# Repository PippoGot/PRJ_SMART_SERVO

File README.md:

# Smart Servo Project
----------------------------------------------------------------

The scope of this repository is to design a new controller board for the MG996R
hobby servo, in order to improve position accuracy and performance.

In particular, the goal is to:

- Implement a more accurate position controller;

- Implement a current controller to limit stall overheating;

- Implement a I2C interface to control the servo, for:
    + current and position readings;
    + flexible and overwritable PID controller & threshold values;
    + calibration routine to estimate motor parameter;
    + possibility of daisy-chaining more servos using a limited number of ports;

More useful things to have are:

- Thermal safety shutdown;

----------------------------------------------------------------
## Folder Structure:

- "DATASHEETS": contains all of the datasheets for the components used,
both in the original controller board and in the new developed board;

- "default servo control board": contains the KiCAD files of the reverse engineered
original servo controller board;

- "MODELS & SIMULATIONS": contains the Simulink and LTSpice models, as well as the
Matlab scripts for parameters and controller tuning;

- "SOURCE": contains all the code for the microcontroller;

- "STM32 PDFs & DATASHEET": contains the documentation of the microcontroller
applied to the board, as well as some useful PDFs for making and programming
embedded projects using the microcontroller itself;

- "STM32F103C8T6 minimum board": contains the KiCAD files of a minimum board
for any embedded project using that specific microcontroller;

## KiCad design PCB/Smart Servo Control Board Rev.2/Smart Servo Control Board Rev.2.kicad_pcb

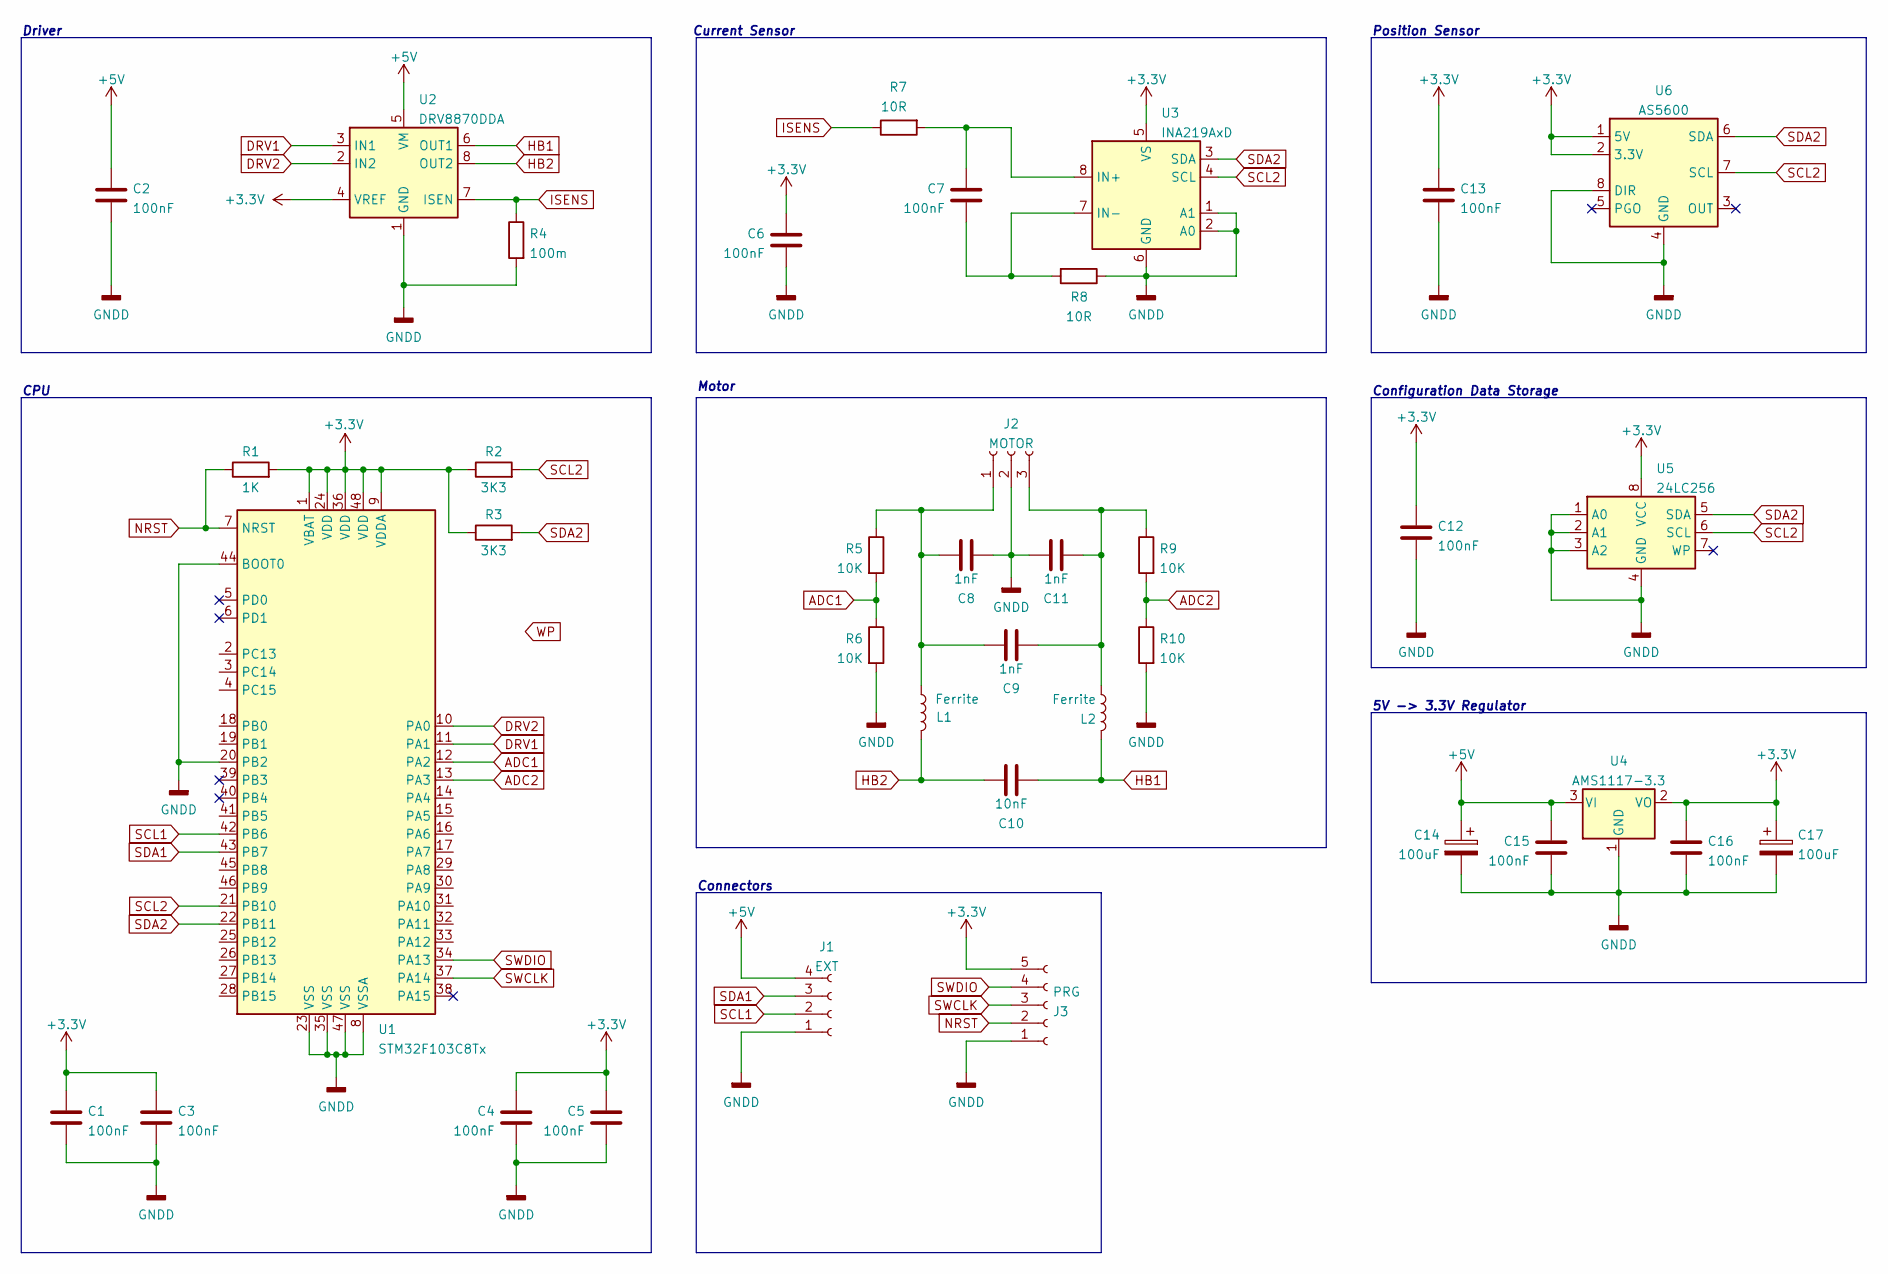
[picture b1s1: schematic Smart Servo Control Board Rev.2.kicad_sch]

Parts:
C1, C2, C3, C4, C5, C6, C7, C12, C13, C15, C16: 100nF; R_0603_1608Metric_Pad0.98x0.95mm_HandSolder
C8, C9, C11: 1nF; R_0603_1608Metric_Pad0.98x0.95mm_HandSolder
C10: 10nF; R_0603_1608Metric_Pad0.98x0.95mm_HandSolder
C14, C17: 100uF; CP_EIA-3216-10_Kemet-I
J1: EXT; Pad_1x04_P2.54mm_Vertical
J2: MOTOR; DC motor 17mm
J3: PRG; PinHeader_1x05_P2.54mm_Vertical_SMD_Pin1Left
L1, L2: Ferrite; R_0603_1608Metric_Pad0.98x0.95mm_HandSolder
R1: 1K; R_0603_1608Metric_Pad0.98x0.95mm_HandSolder
R2, R3: 3K3; R_0603_1608Metric_Pad0.98x0.95mm_HandSolder
R4: 100m; R_1206_3216Metric_Pad1.30x1.75mm_HandSolder
R5, R6, R9, R10: 10K; R_0603_1608Metric_Pad0.98x0.95mm_HandSolder
R7, R8: 10R; R_0603_1608Metric_Pad0.98x0.95mm_HandSolder
U1: STM32F103C8Tx; LQFP-48_7x7mm_P0.5mm
U2: DRV8870DDA; SOIC-8-1EP_3.9x4.9mm_P1.27mm_EP2.514x3.2mm
U3: INA219AxD; SOT-23-8
U4: AMS1117-3.3; SOT-223-3_TabPin2
U5: 24LC256; SO-8_3.9x4.9mm_P1.27mm
U6: AS5600; SO-8_3.9x4.9mm_P1.27mm

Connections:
+3V3: C1.2, C3.2, C4.2, C5.2, C6.2, C12.2, C13.2, C16.1, C17.1, J3.5, R1.2, R2.1, R3.1, U1.1 (VBAT), U1.9 (VDDA), U1.24 (VDD), U1.36 (VDD), U1.48 (VDD), U2.4 (VREF), U3.5 (VS), U4.2 (VO), U5.8 (VCC), U6.1 (5V), U6.2 (3.3V)
+5V: C2.2, C14.1, C15.1, J1.4, U2.5 (VM), U4.3 (VI)
ADC1: R5.2, R6.1, U1.12 (PA2)
ADC2: R9.2, R10.1, U1.13 (PA3)
DRV1: U1.11 (PA1), U2.3 (IN1)
DRV2: U1.10 (PA0), U2.2 (IN2)
GNDD: C1.1, C2.1, C3.1, C4.1, C5.1, C6.1, C8.2, C11.1, C12.1, C13.1, C14.2, C15.2, C16.2, C17.2, J1.1, J2.2, J3.1, R4.2, R6.2, R8.1, R10.2, U1.8 (VSSA), U1.20 (PB2), U1.23 (VSS), U1.35 (VSS), U1.44 (BOOT0), U1.47 (VSS), U2.1 (GND), U2.9 (GND), U3.1 (A1), U3.2 (A0), U3.6 (GND), U4.1 (GND), U5.1 (A0), U5.2 (A1), U5.3 (A2), U5.4 (GND), U6.4 (GND), U6.8 (DIR)
HB1: C10.2, L2.2, U2.6 (OUT1)
HB2: C10.1, L1.2, U2.8 (OUT2)
ISENS: R4.1, R7.1, U2.7 (ISEN)
NRST: J3.2, R1.1, U1.7 (NRST)
unnamed: C7.1, R7.2, U3.8 (IN+)
unnamed: C7.2, R8.2, U3.7 (IN-)
unnamed: C8.1, C9.1, J2.1, L1.1, R5.1
unnamed: C9.2, C11.2, J2.3, L2.1, R9.1
SCL1: J1.2, U1.42 (PB6)
SCL2: R2.2, U1.21 (PB10), U3.4 (SCL), U5.6 (SCL), U6.7 (SCL)
SDA1: J1.3, U1.43 (PB7)
SDA2: R3.2, U1.22 (PB11), U3.3 (SDA), U5.5 (SDA), U6.6 (SDA)
SWCLK: J3.3, U1.37 (PA14)
SWDIO: J3.4, U1.34 (PA13)

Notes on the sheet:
Current Sensor
Position Sensor
Motor
5V -> 3.3V Regulator
Driver
CPU
Connectors
Configuration Data Storage

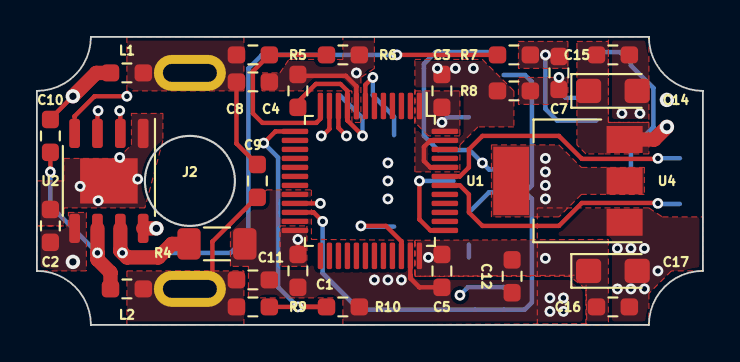
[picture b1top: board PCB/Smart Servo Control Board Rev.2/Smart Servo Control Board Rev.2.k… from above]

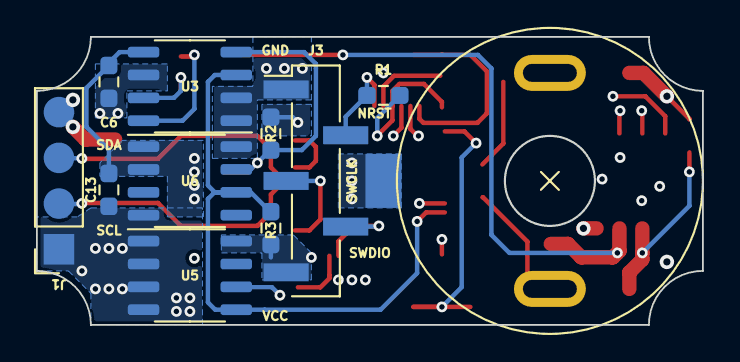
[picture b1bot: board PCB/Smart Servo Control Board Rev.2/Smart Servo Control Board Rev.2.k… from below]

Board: 4 copper layers, 37.0 x 16.0 mm, 38 parts (10 on the bottom side), 21 nets.

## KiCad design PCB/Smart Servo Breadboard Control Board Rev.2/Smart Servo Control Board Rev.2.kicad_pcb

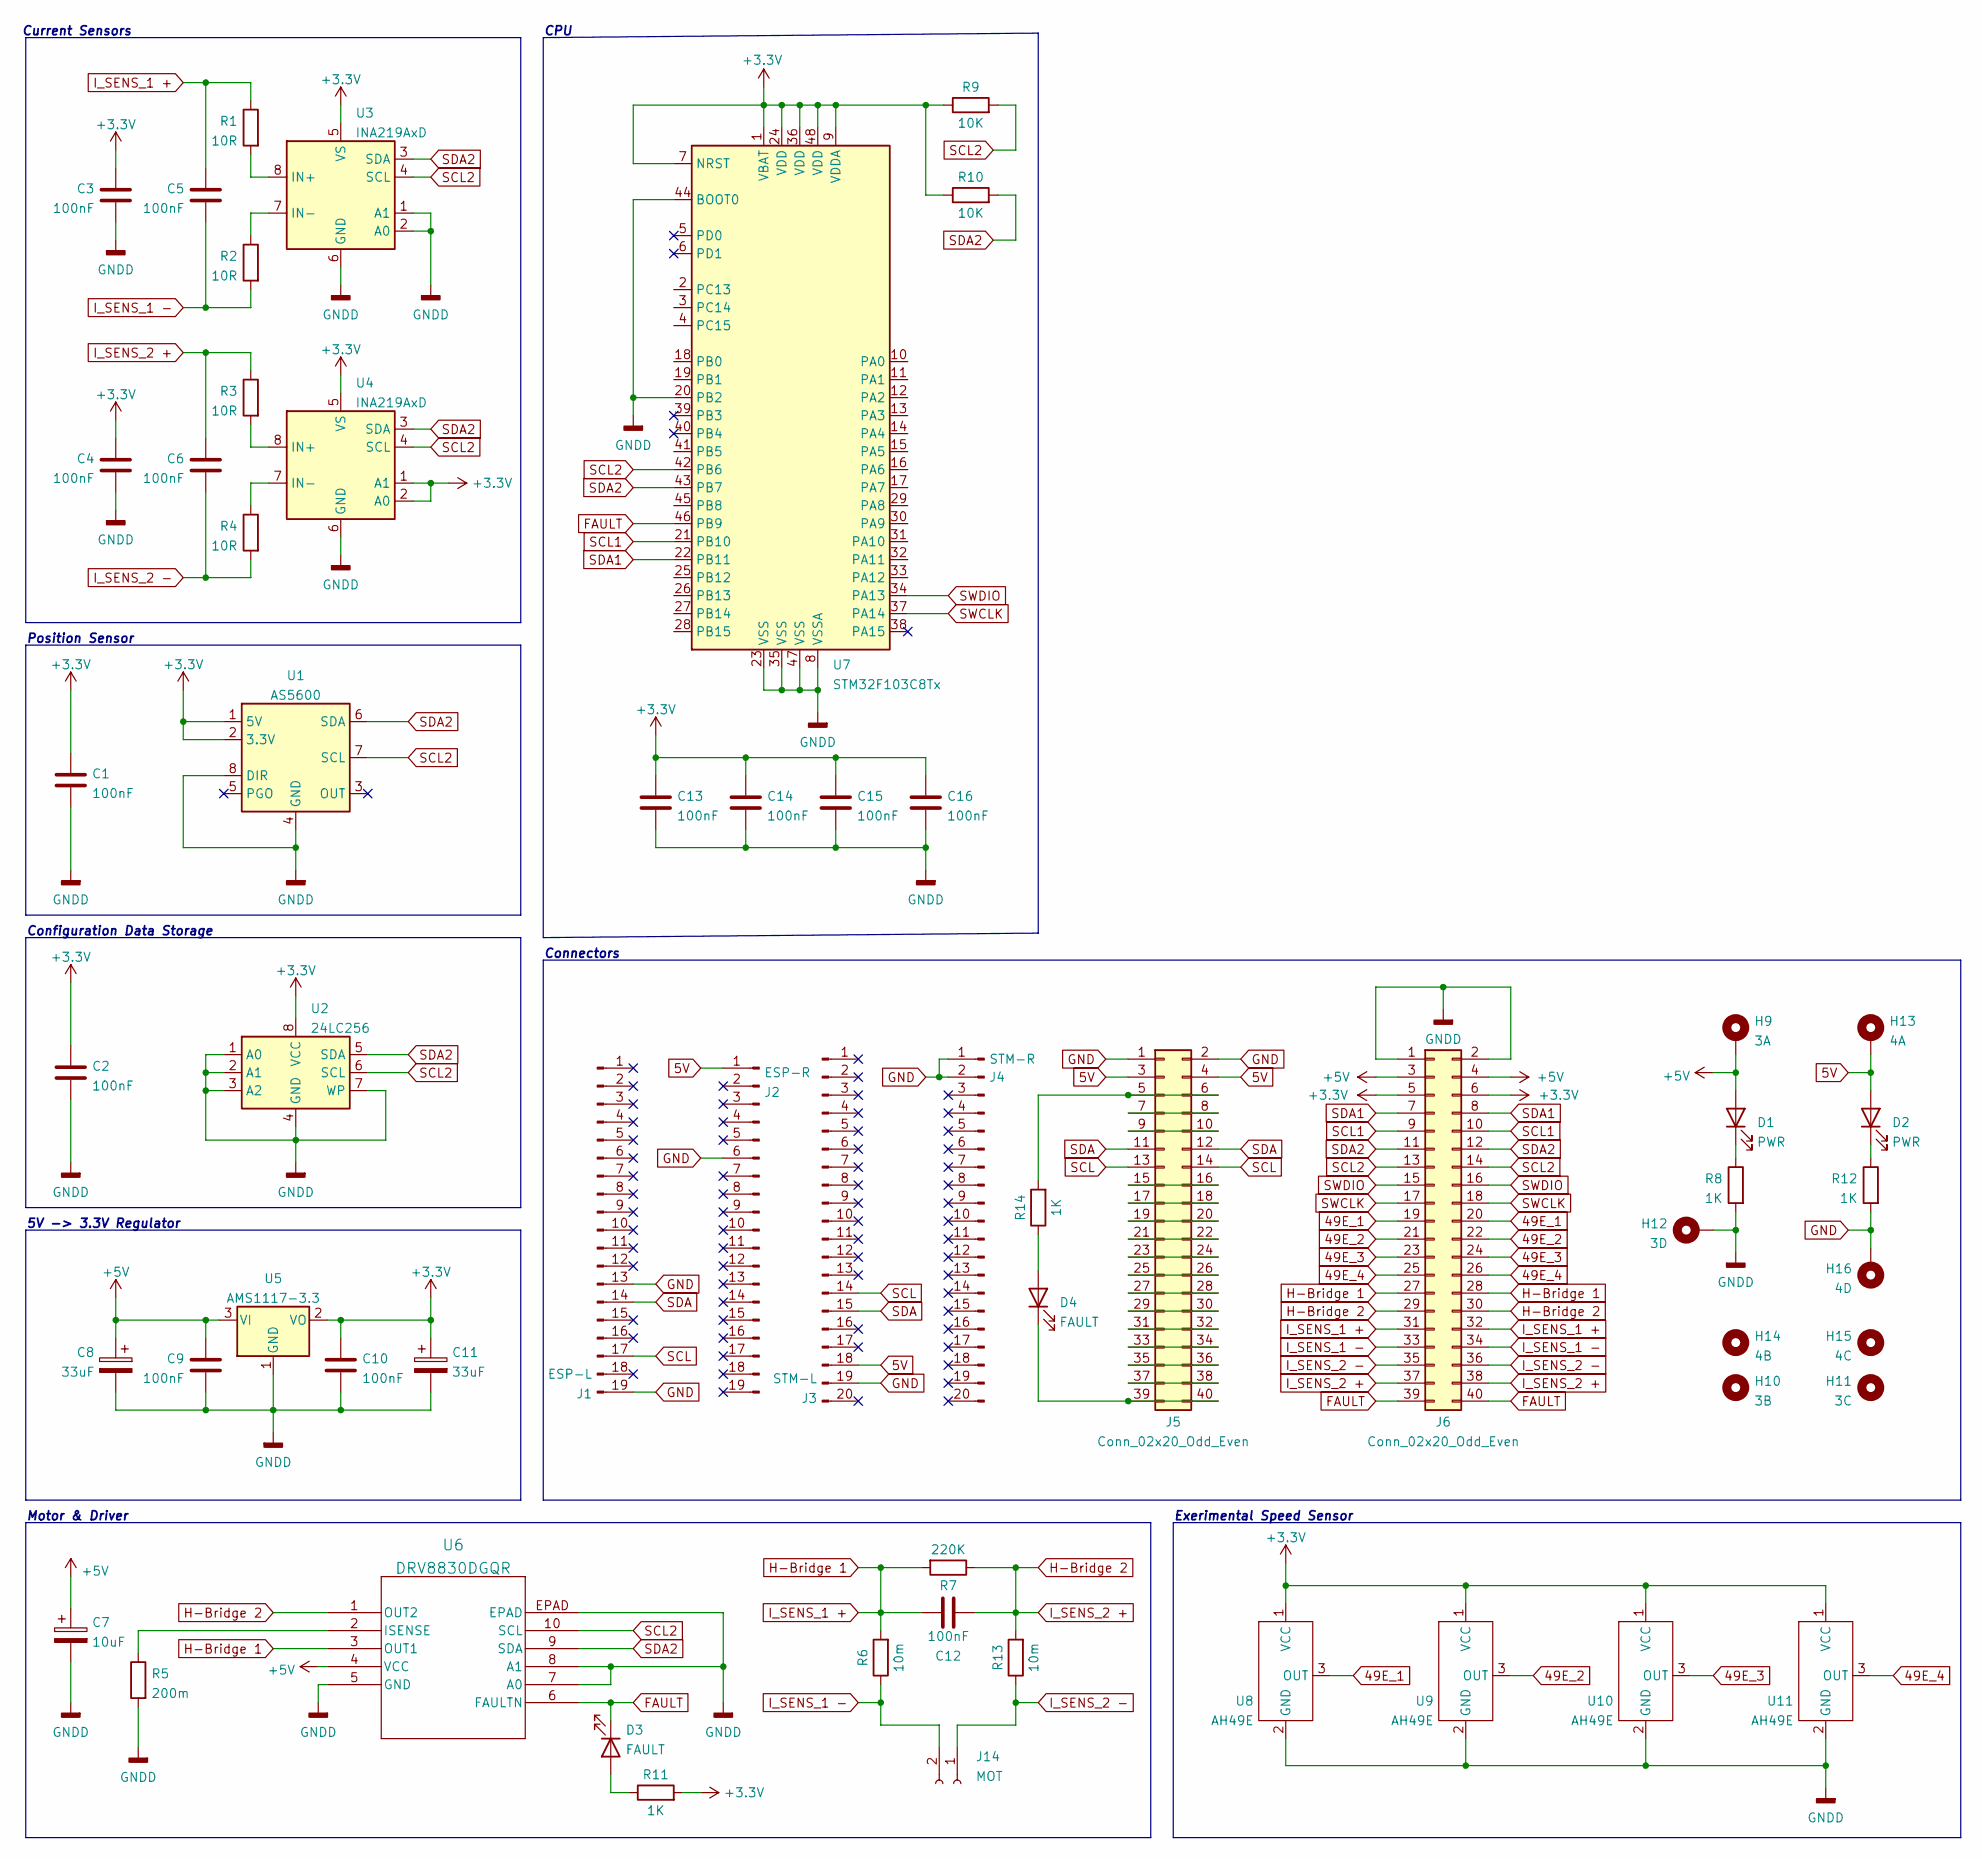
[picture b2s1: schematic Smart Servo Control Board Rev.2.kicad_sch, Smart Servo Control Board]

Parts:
C1, C2, C3, C4, C5, C6, C9, C10, C12, C13, C14, C15, C16: 100nF; R_0603_1608Metric_Pad0.98x0.95mm_HandSolder
C7: 10uF; R_0603_1608Metric_Pad0.98x0.95mm_HandSolder
C8, C11: 33uF; R_0603_1608Metric_Pad0.98x0.95mm_HandSolder
D1, D2: PWR; D_1206_3216Metric_Pad1.42x1.75mm_HandSolder
D3, D4: FAULT; D_1206_3216Metric_Pad1.42x1.75mm_HandSolder
H9: 3A; MountingHole_4.3mm_M4_DIN965_Pad_TopBottom
H10: 3B; MountingHole_4.3mm_M4
H11: 3C; MountingHole_4.3mm_M4
H12: 3D; MountingHole_4.3mm_M4_DIN965_Pad_TopBottom
H13: 4A; MountingHole_4.3mm_M4_DIN965_Pad_TopBottom
H14: 4B; MountingHole_4.3mm_M4
H15: 4C; MountingHole_4.3mm_M4
H16: 4D; MountingHole_4.3mm_M4_DIN965_Pad_TopBottom
J1: ESP-L; PinSocket_1x19_P2.54mm_Vertical
J2: ESP-R; PinSocket_1x19_P2.54mm_Vertical
J3: STM-L; PinSocket_1x20_P2.54mm_Vertical
J4: STM-R; PinSocket_1x20_P2.54mm_Vertical
J5, J6: Conn_02x20_Odd_Even; PinSocket_2x20_P2.54mm_Vertical
J14: MOT; PinSocket_1x02_P2.54mm_Vertical
R1, R2, R3, R4: 10R; R_0603_1608Metric_Pad0.98x0.95mm_HandSolder
R5: 200m; R_1206_3216Metric_Pad1.30x1.75mm_HandSolder
R6, R13: 10m; R_0603_1608Metric_Pad0.98x0.95mm_HandSolder
R7: 220K; R_0603_1608Metric_Pad0.98x0.95mm_HandSolder
R8, R11, R12, R14: 1K; R_0603_1608Metric_Pad0.98x0.95mm_HandSolder
R9, R10: 10K; R_0603_1608Metric_Pad0.98x0.95mm_HandSolder
U1: AS5600; SO-8_3.9x4.9mm_P1.27mm
U2: 24LC256; SO-8_3.9x4.9mm_P1.27mm
U3, U4: INA219AxD; SOIC-8_3.9x4.9mm_P1.27mm
U5: AMS1117-3.3; SOT-223-3_TabPin2
U6: DRV8830DGQR; DGQ10_2P18X1P72
U7: STM32F103C8Tx; LQFP-48_7x7mm_P0.5mm
U8, U9: AH49E; TO-92S
U10, U11: AH49E; SOT-23

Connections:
5V: D2.2 (A), H13.1, J2.1, J3.18, J5.3, J5.4
49E_1: J6.19, J6.20, U8.3 (OUT)
49E_2: J6.21, J6.22, U9.3 (OUT)
49E_3: J6.23, J6.24, U10.3 (OUT)
49E_4: J6.25, J6.26, U11.3 (OUT)
+3V3: C1.2, C2.2, C3.2, C4.2, C10.1, C11.1, C13.2, C14.2, C15.2, C16.2, J6.5, J6.6, R9.1, R10.1, R11.2, U1.1 (5V), U1.2 (3.3V), U2.8 (VCC), U3.5 (VS), U4.1 (A1), U4.2 (A0), U4.5 (VS), U5.2 (VO), U7.1 (VBAT), U7.7 (NRST), U7.9 (VDDA), U7.24 (VDD), U7.36 (VDD), U7.48 (VDD), U8.1 (VCC), U9.1 (VCC), U10.1 (VCC), U11.1 (VCC)
+5V: C7.1, C8.1, C9.1, D1.2 (A), H9.1, J6.3, J6.4, U5.3 (VI), U6.4 (VCC)
FAULT: D3.1 (K), J6.39, J6.40, U6.6 (FAULTN), U7.46 (PB9)
GND: H16.1, J1.13, J1.19, J2.6, J3.19, J4.1, J4.2, J5.1, J5.2, R12.2
GNDD: C1.1, C2.1, C3.1, C4.1, C7.2, C8.2, C9.2, C10.2, C11.2, C13.1, C14.1, C15.1, C16.1, H12.1, J6.1, J6.2, R5.2, R8.2, U1.4 (GND), U1.8 (DIR), U2.1 (A0), U2.2 (A1), U2.3 (A2), U2.4 (GND), U2.7 (WP), U3.1 (A1), U3.2 (A0), U3.6 (GND), U4.6 (GND), U5.1 (GND), U6.5 (GND), U6.7 (A0), U6.8 (A1), U6.EPAD, U6.V, U7.8 (VSSA), U7.20 (PB2), U7.23 (VSS), U7.35 (VSS), U7.44 (BOOT0), U7.47 (VSS), U8.2 (GND), U9.2 (GND), U10.2 (GND), U11.2 (GND)
H-Bridge 1: C5.1, C12.1, J6.27, J6.28, J6.31, J6.32, R1.1, R6.2, R7.2, U6.3 (OUT1)
H-Bridge 2: C6.1, C12.2, J6.29, J6.30, J6.37, J6.38, R3.1, R7.1, R13.2, U6.1 (OUT2)
I_SENS_1 -: C5.2, J6.33, J6.34, J14.2, R2.2, R6.1
I_SENS_2 -: C6.2, J6.35, J6.36, J14.1, R4.2, R13.1
unnamed: D1.1 (K), R8.1
unnamed: D2.1 (K), R12.1
unnamed: D3.2 (A), R11.1
unnamed: D4.2 (A), R14.1
unnamed: J5.5, J5.6, R14.2
unnamed: J5.7, J5.8
unnamed: J5.9, J5.10
unnamed: J5.15, J5.16
unnamed: J5.17, J5.18
unnamed: J5.19, J5.20
unnamed: J5.21, J5.22
unnamed: J5.23, J5.24
unnamed: J5.25, J5.26
unnamed: J5.27, J5.28
unnamed: J5.29, J5.30
unnamed: J5.31, J5.32
unnamed: J5.33, J5.34
unnamed: J5.35, J5.36
unnamed: J5.37, J5.38
unnamed: D4.1 (K), J5.39, J5.40
unnamed: R1.2, U3.8 (IN+)
unnamed: R2.1, U3.7 (IN-)
unnamed: R3.2, U4.8 (IN+)
unnamed: R4.1, U4.7 (IN-)
unnamed: R5.1, U6.2 (ISENSE)
SCL: J1.17, J3.14, J5.13, J5.14
SCL1: J6.9, J6.10, U7.21 (PB10)
SCL2: J6.13, J6.14, R9.2, U1.7 (SCL), U2.6 (SCL), U3.4 (SCL), U4.4 (SCL), U6.10 (SCL), U7.42 (PB6)
SDA: J1.14, J3.15, J5.11, J5.12
SDA1: J6.7, J6.8, U7.22 (PB11)
SDA2: J6.11, J6.12, R10.2, U1.6 (SDA), U2.5 (SDA), U3.3 (SDA), U4.3 (SDA), U6.9 (SDA), U7.43 (PB7)
SWCLK: J6.17, J6.18, U7.37 (PA14)
SWDIO: J6.15, J6.16, U7.34 (PA13)

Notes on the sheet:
Configuration Data Storage
Position Sensor
CPU
Motor & Driver
5V -> 3.3V Regulator
Current Sensors
Connectors
Exerimental Speed Sensor

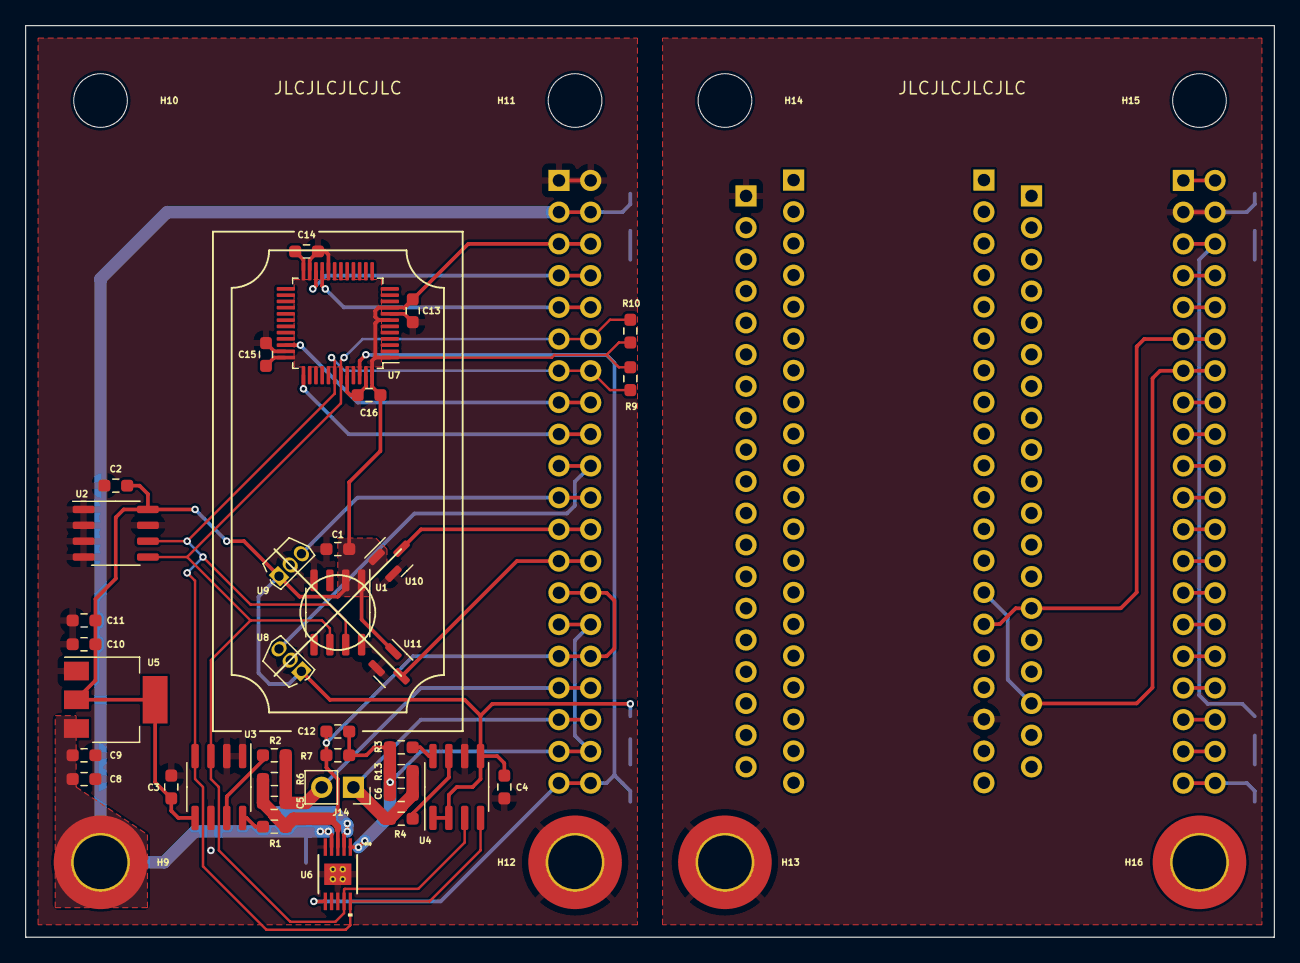
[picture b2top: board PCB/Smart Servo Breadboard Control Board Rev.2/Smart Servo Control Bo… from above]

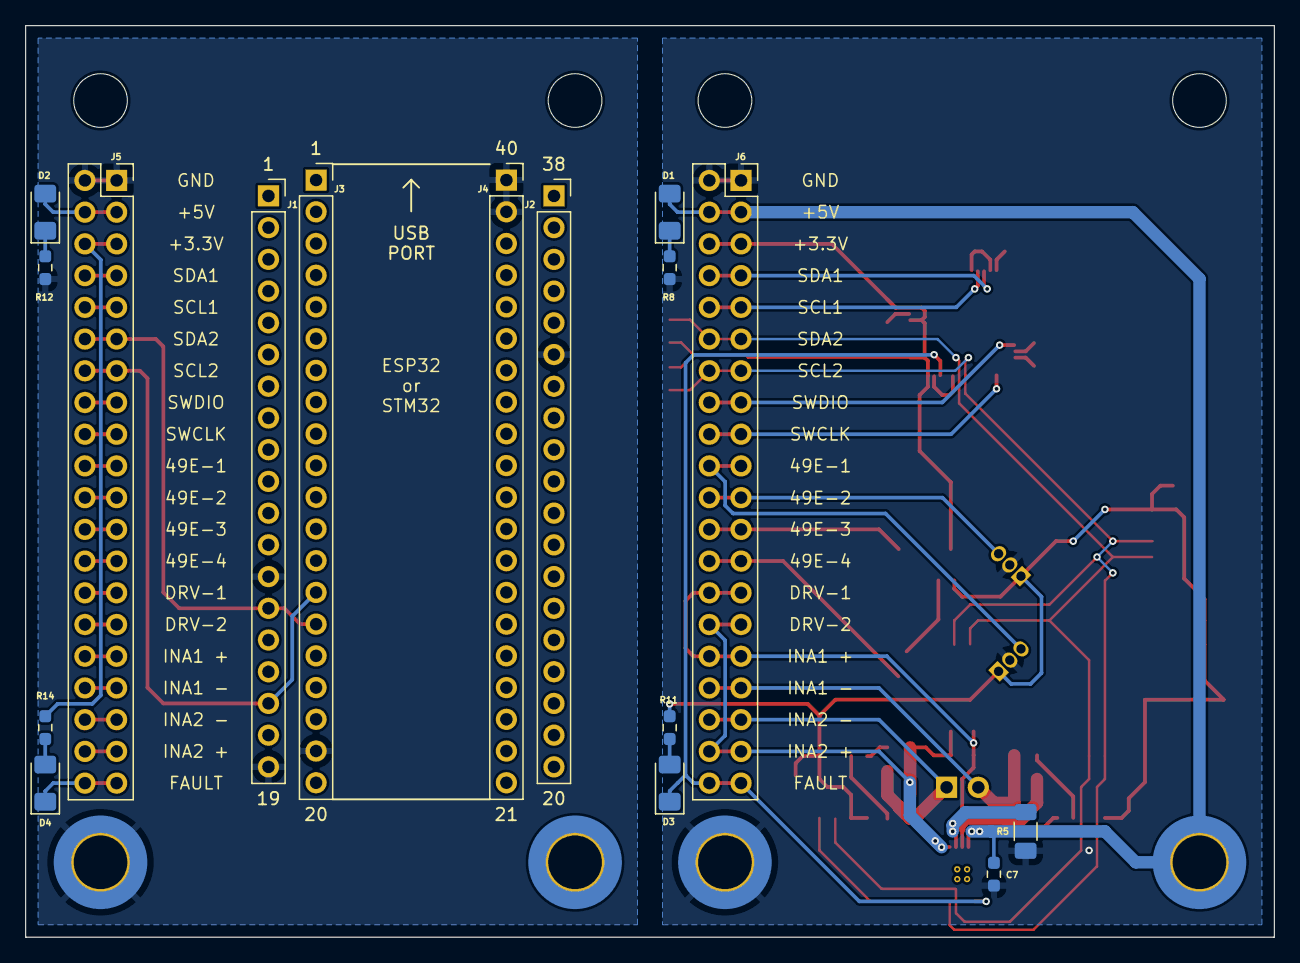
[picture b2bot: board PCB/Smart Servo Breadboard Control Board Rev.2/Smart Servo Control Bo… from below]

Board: 4 copper layers, 100.0 x 73.0 mm, 60 parts (16 on the bottom side), 47 nets.

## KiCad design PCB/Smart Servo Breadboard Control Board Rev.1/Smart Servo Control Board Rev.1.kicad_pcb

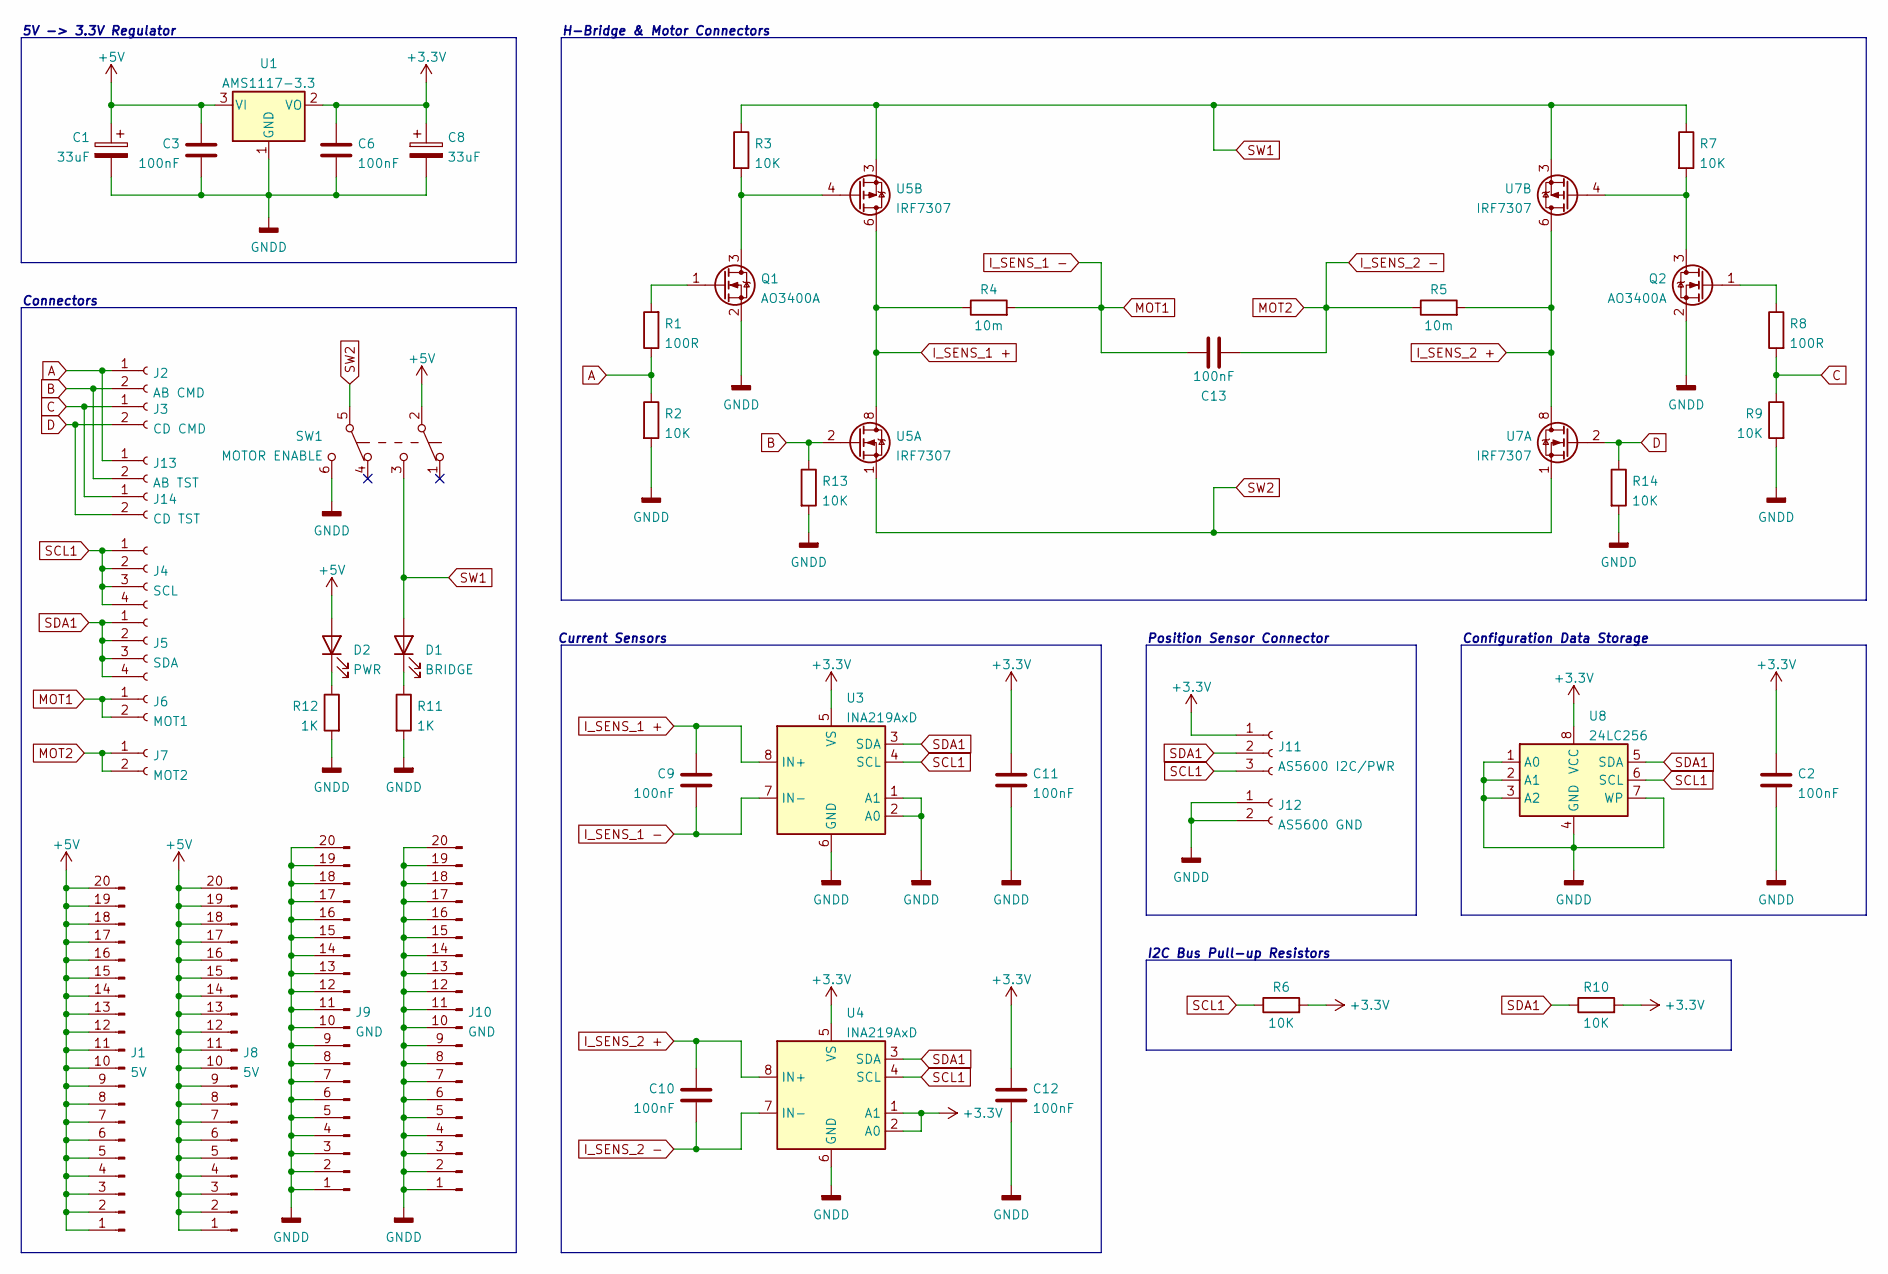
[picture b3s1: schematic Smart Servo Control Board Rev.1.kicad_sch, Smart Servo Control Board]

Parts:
C1, C8: 33uF; CP_Radial_D5.0mm_P2.50mm
C2, C3, C6, C9, C10, C11, C12, C13: 100nF; C_Disc_P2.54mm
D1: BRIDGE; D_1206_3216Metric_Pad1.42x1.75mm_HandSolder
D2: PWR; D_1206_3216Metric_Pad1.42x1.75mm_HandSolder
J1, J8: 5V; PinHeader_1x20_P2.54mm_Vertical
J2: AB CMD; PinHeader_1x02_P2.54mm_Vertical
J3: CD CMD; PinHeader_1x02_P2.54mm_Vertical
J4: SCL; PinHeader_1x04_P2.54mm_Vertical
J5: SDA; PinHeader_1x04_P2.54mm_Vertical
J6: MOT1; PinHeader_1x02_P2.54mm_Vertical
J7: MOT2; PinHeader_1x02_P2.54mm_Vertical
J9, J10: GND; PinHeader_1x20_P2.54mm_Vertical
J11: AS5600 I2C/PWR; PinHeader_1x03_P2.54mm_Vertical
J12: AS5600 GND; PinHeader_1x02_P2.54mm_Vertical
J13: AB TST; PinHeader_1x02_P2.54mm_Vertical
J14: CD TST; PinHeader_1x02_P2.54mm_Vertical
Q1, Q2: AO3400A; SOT-23 Breadboard Adapter
R1, R8: 100R; R_0603_1608Metric_Pad0.98x0.95mm_HandSolder
R2, R3, R6, R7, R9, R10, R13, R14: 10K; R_1206_3216Metric_Pad1.30x1.75mm_HandSolder
R4, R5: 10m; R_0603_1608Metric_Pad0.98x0.95mm_HandSolder
R11, R12: 1K; R_1206_3216Metric_Pad1.30x1.75mm_HandSolder
SW1: MOTOR ENABLE; DPDT Pushbutton
U1: AMS1117-3.3; SOT-223-3_TabPin2
U3, U4: INA219AxD; SOIC-8 Breadboard Adapter
U5, U7: IRF7307; SOIC-8 Breadboard Adapter
U8: 24LC256; SOIC-8 Breadboard Adapter

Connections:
+3V3: C2.2, C6.1, C8.1, C11.2, C12.2, J11.1, R6.2, R10.2, U1.2 (VO), U3.5 (VS), U4.1 (A1), U4.2 (A0), U4.5 (VS), U8.8 (VCC)
+5V: C1.1, C3.1, D2.2 (A), J1.1, J1.2, J1.3, J1.4, J1.5, J1.6, J1.7, J1.8, J1.9, J1.10, J1.11, J1.12, J1.13, J1.14, J1.15, J1.16, J1.17, J1.18, J1.19, J1.20, J8.1, J8.2, J8.3, J8.4, J8.5, J8.6, J8.7, J8.8, J8.9, J8.10, J8.11, J8.12, J8.13, J8.14, J8.15, J8.16, J8.17, J8.18, J8.19, J8.20, SW1.2 (B), U1.3 (VI)
A: J2.1, J13.1, R1.1, R2.1
B: J2.2, J13.2, R13.1, U5.2
C: J3.1, J14.1, R8.2, R9.1
D: J3.2, J14.2, R14.1, U7.2
GNDD: C1.2, C2.1, C3.2, C6.2, C8.2, C11.1, C12.1, J9.1, J9.2, J9.3, J9.4, J9.5, J9.6, J9.7, J9.8, J9.9, J9.10, J9.11, J9.12, J9.13, J9.14, J9.15, J9.16, J9.17, J9.18, J9.19, J9.20, J10.1, J10.2, J10.3, J10.4, J10.5, J10.6, J10.7, J10.8, J10.9, J10.10, J10.11, J10.12, J10.13, J10.14, J10.15, J10.16, J10.17, J10.18, J10.19, J10.20, J12.1, J12.2, Q1.2 (S), Q2.2 (S), R2.2, R9.2, R11.2, R12.2, R13.2, R14.2, SW1.6 (C), U1.1 (GND), U3.1 (A1), U3.2 (A0), U3.6 (GND), U4.6 (GND), U8.1 (A0), U8.2 (A1), U8.3 (A2), U8.4 (GND), U8.7 (WP)
I_SENS_1 +: C9.1, R4.1, U3.8 (IN+), U5.5, U5.6, U5.7, U5.8
I_SENS_1 -: C9.2, C13.1, J6.1, J6.2, R4.2, U3.7 (IN-)
I_SENS_2 +: C10.1, R5.2, U4.8 (IN+), U7.5, U7.6, U7.7, U7.8
I_SENS_2 -: C10.2, C13.2, J7.1, J7.2, R5.1, U4.7 (IN-)
unnamed: D1.1 (K), R11.1
unnamed: D2.1 (K), R12.1
unnamed: Q1.1 (G), R1.2
unnamed: Q1.3 (D), R3.2, U5.4
unnamed: Q2.1 (G), R8.1
unnamed: Q2.3 (D), R7.2, U7.4
SCL1: J4.1, J4.2, J4.3, J4.4, J11.3, R6.1, U3.4 (SCL), U4.4 (SCL), U8.6 (SCL)
SDA1: J5.1, J5.2, J5.3, J5.4, J11.2, R10.1, U3.3 (SDA), U4.3 (SDA), U8.5 (SDA)
SW1: D1.2 (A), R3.1, R7.1, SW1.3 (C), U5.3, U7.3
SW2: SW1.5 (B), U5.1, U7.1

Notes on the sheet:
Configuration Data Storage
Position Sensor Connector
I2C Bus Pull-up Resistors
H-Bridge & Motor Connectors
5V -> 3.3V Regulator
Current Sensors
Connectors

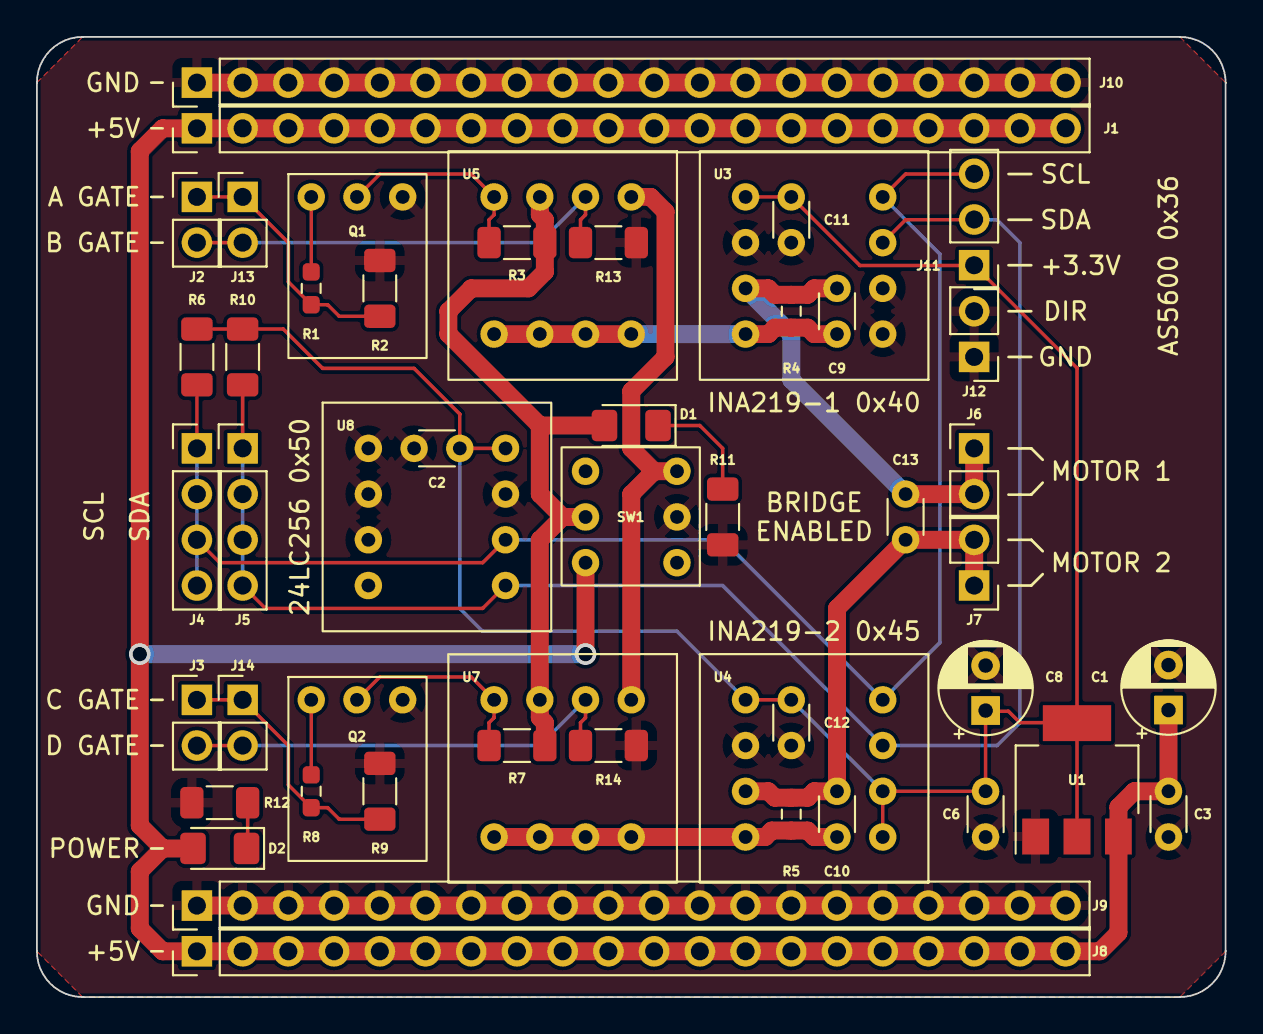
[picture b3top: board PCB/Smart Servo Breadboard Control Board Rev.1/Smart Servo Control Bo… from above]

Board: 2 copper layers, 66.0 x 53.3 mm, 49 parts (0 on the bottom side), 21 nets.
